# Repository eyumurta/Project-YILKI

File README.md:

This is the first Prototype of Open Plc Controller Board Yılkı.This project devoloped with Eagle
Project started 2024.
First Protype doesn't have built in Power,mcu circuits. This PT1 is only creating for testing input,output and Rs485 line.
I'm not a hardware engineer so project maybe have faulty designs.This Board using Stm32f0 Discovery board to handle inputs and outputs.
You can see inputs state by LED.But power calculations are wrong so I'm not soldered the Leds and their resistors.In theory boards outputs can drive relay but not tested. 

Input Side:
Inputs Are Designed sink (0v Common).Protected by TVS diode and optocoupler.Added RC filter for ripples.

Output Side:
Outputs are Designed source(24V Common).Outputs Protected by Optocoupler and reverse diode for relay.

Full Duplex RS-485:
This circuit is Full Duplex Rs-485 line

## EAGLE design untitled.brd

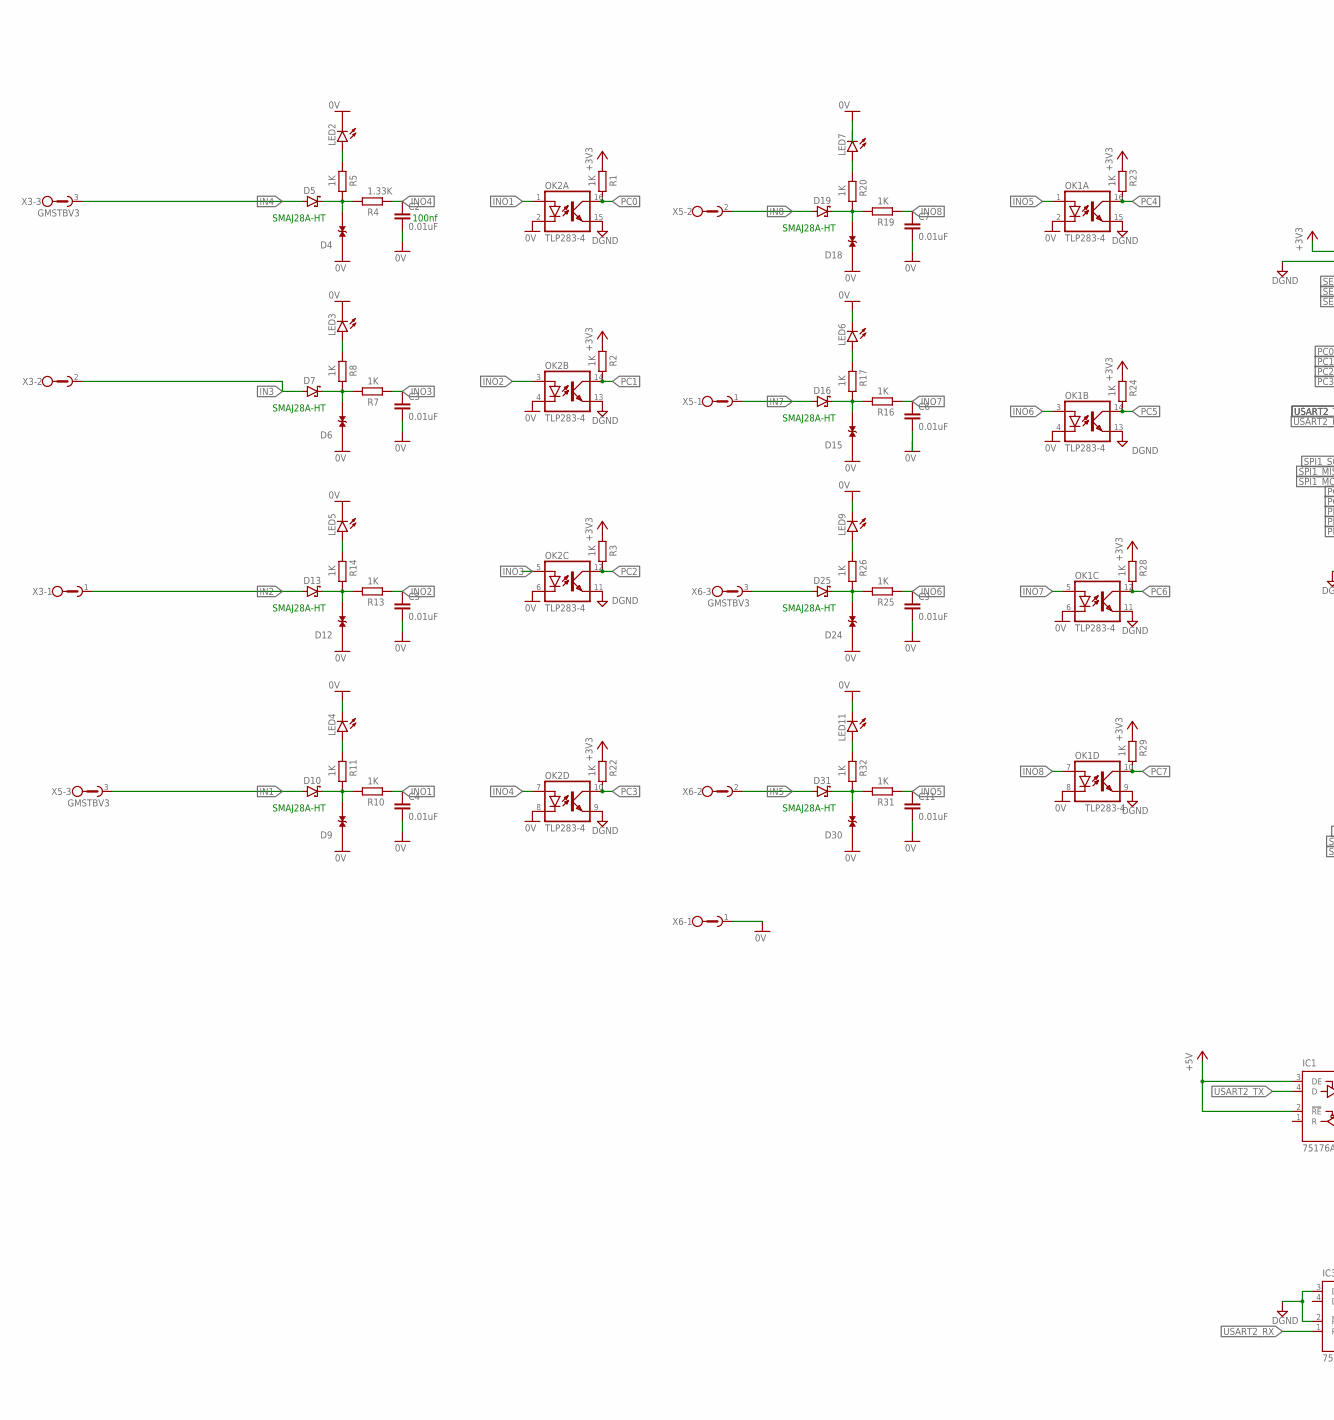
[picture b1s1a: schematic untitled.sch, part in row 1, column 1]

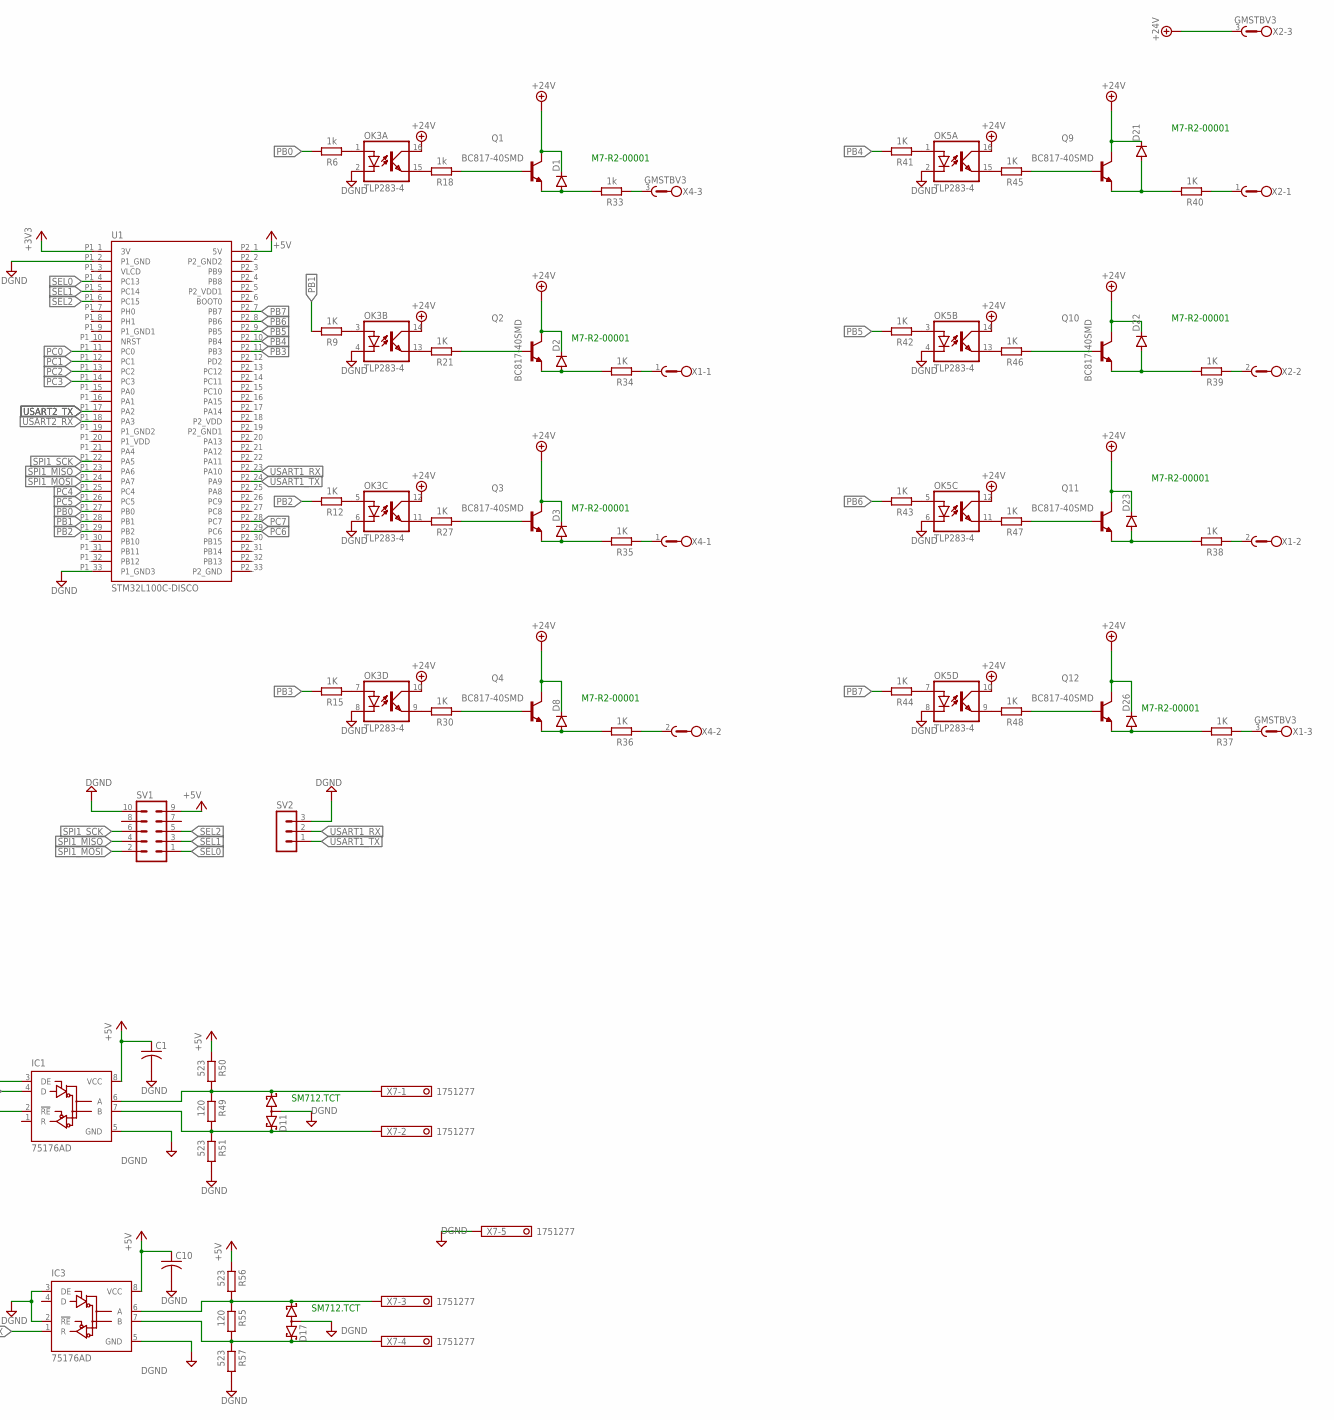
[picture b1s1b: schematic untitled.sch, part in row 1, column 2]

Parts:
C1, C10: C-USC0805; C0805
C2, C3, C4, C5, C6, C7, C9, C11: 0.01uF; C0805
D1, D2, D3, D8, D21, D22, D23, D26: S1M; SMA
D4, D6, D9, D12, D15, D18, D24, D30: SMAJ28CA; DIOM4325X250N
D5, D7, D10, D13, D16, D19, D25, D31: SCHOTTKY-DIODESMD; SMB
D11, D17: BAS40-06; SOT23
IC1, IC3: 75176AD; D_R-PDSO-G8
LED2, LED3, LED4, LED5, LED6, LED7, LED9, LED11: LEDCHIP-LED0805; CHIP-LED0805
OK1, OK2, OK3, OK5: TLP283-4; MINI-FLAT-16
Q1, Q2, Q3, Q4, Q9, Q10, Q11, Q12: BC817-40SMD; SOT23-BEC
R1, R2, R3, R5, R7, R8, R9, R10, R11, R12, R13, R14, R15, R16, R17, R19, R20, R21, R22, R23, R24, R25, R26, R27, R28, R29, R30, R31, R32, R34, R35, R36, R37, R38, R39, R40, R41, R42, R43, R44, R45, R46, R47, R48: 1K; R0805
R4: 1.33K; R0805
R6, R18, R33: 1k; R0805
R49, R55: 120; R0805
R50, R51, R56, R57: 523; R0805
SV1: MA05-2
SV2: MA03-1
U1: STM32L100C-DISCO; DEV_STM32L100C-DISCO
X1, X2, X3, X4, X5, X6: GMSTBV3
X7: 1751277

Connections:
0V: C2.2, C3.2, C4.2, C5.2, C6.2, C7.2, C9.2, C11.2, D4.1, D6.1, D9.1, D12.1, D15.1, D18.1, D24.1, D30.1, LED2.C, LED3.C, LED4.C, LED5.C, LED6.C, LED7.C, LED9.C, LED11.C, OK1.2 (C), OK1.4 (C), OK1.6 (C), OK1.8 (C), OK2.2 (C), OK2.4 (C), OK2.6 (C), OK2.8 (C), X6.1
+3V3: R1.2, R2.2, R3.2, R22.2, R23.2, R24.2, R28.2, R29.2, U1.P1_1 (3V)
+5V: C1.1, C10.1, IC1.2 (!RE), IC1.3 (DE), IC1.8 (VCC), IC3.8 (VCC), R50.2, R56.2, SV1.9, U1.P2_1 (5V)
+24V: D1.C, D2.C, D3.C, D8.C, D21.C, D22.C, D23.C, D26.C, OK3.10 (COL), OK3.12 (COL), OK3.14 (COL), OK3.16 (COL), OK5.10 (COL), OK5.12 (COL), OK5.14 (COL), OK5.16 (COL), Q1.C, Q2.C, Q3.C, Q4.C, Q9.C, Q10.C, Q11.C, Q12.C, X2.3
DGND: C1.2, C10.2, D11.3 (AA), D17.3 (AA), IC1.5 (GND), IC3.2 (!RE), IC3.3 (DE), IC3.5 (GND), OK1.9 (EMIT), OK1.11 (EMIT), OK1.13 (EMIT), OK1.15 (EMIT), OK2.9 (EMIT), OK2.11 (EMIT), OK2.13 (EMIT), OK2.15 (EMIT), OK3.2 (C), OK3.4 (C), OK3.6 (C), OK3.8 (C), OK5.2 (C), OK5.4 (C), OK5.6 (C), OK5.8 (C), R51.1, R57.1, SV1.10, SV2.3, U1.P1_2 (P1_GND), U1.P1_33 (P1_GND3), X7.5
IN1: D10.A, X5.3
IN2: D13.A, X3.1
IN3: D7.A, X3.2
IN4: D5.A, X3.3
IN5: D31.A, X6.2
IN7: D16.A, X5.1
IN8: D19.A, X5.2
INO1: C4.1, OK2.1 (A), R10.2
INO2: C5.1, OK2.3 (A), R13.2
INO3: C3.1, OK2.5 (A), R7.2
INO4: C2.1, OK2.7 (A), R4.2
INO5: C11.1, OK1.1 (A), R31.2
INO6: C9.1, OK1.3 (A), R25.2
INO7: C6.1, OK1.5 (A), R16.2
INO8: C7.1, OK1.7 (A), R19.2
unnamed: LED2.A, R5.2
unnamed: LED3.A, R8.2
unnamed: LED4.A, R11.2
unnamed: LED5.A, R14.2
unnamed: LED6.A, R17.2
unnamed: LED7.A, R20.2
unnamed: LED9.A, R26.2
unnamed: LED11.A, R32.2
unnamed: D4.2, D5.C, R4.1, R5.1
unnamed: D6.2, D7.C, R7.1, R8.1
unnamed: D12.2, D13.C, R13.1, R14.1
unnamed: D9.2, D10.C, R10.1, R11.1
unnamed: D18.2, D19.C, R19.1, R20.1
unnamed: D15.2, D16.C, R16.1, R17.1
unnamed: D24.2, D25.C, R25.1, R26.1
unnamed: D30.2, D31.C, R31.1, R32.1
unnamed: OK3.1 (A), R6.2
unnamed: OK3.3 (A), R9.2
unnamed: OK3.5 (A), R12.2
unnamed: OK3.7 (A), R15.2
unnamed: OK3.15 (EMIT), R18.1
unnamed: OK3.13 (EMIT), R21.1
unnamed: OK3.11 (EMIT), R27.1
unnamed: OK3.9 (EMIT), R30.1
unnamed: Q4.B, R30.2
unnamed: Q3.B, R27.2
unnamed: Q2.B, R21.2
unnamed: Q1.B, R18.2
unnamed: R33.2, X4.3
unnamed: R34.2, X1.1
unnamed: R35.2, X4.1
unnamed: D25.A, X6.3
unnamed: OK5.1 (A), R41.2
unnamed: OK5.15 (EMIT), R45.1
unnamed: OK5.3 (A), R42.2
unnamed: OK5.13 (EMIT), R46.1
unnamed: OK5.5 (A), R43.2
unnamed: OK5.11 (EMIT), R47.1
unnamed: OK5.7 (A), R44.2
unnamed: OK5.9 (EMIT), R48.1
unnamed: D1.A, Q1.E, R33.1
unnamed: R36.2, X4.2
unnamed: D2.A, Q2.E, R34.1
unnamed: D3.A, Q3.E, R35.1
unnamed: D8.A, Q4.E, R36.1
unnamed: D26.A, Q12.E, R37.1
unnamed: D23.A, Q11.E, R38.1
unnamed: D22.A, Q10.E, R39.1
unnamed: Q12.B, R48.2
unnamed: Q11.B, R47.2
unnamed: Q10.B, R46.2
unnamed: Q9.B, R45.2
unnamed: R37.2, X1.3
unnamed: R38.2, X1.2
unnamed: R39.2, X2.2
unnamed: R40.2, X2.1
unnamed: D21.A, Q9.E, R40.1
unnamed: D11.1 (K1), IC1.6 (A), R49.2, R50.1, X7.1
unnamed: D11.2 (K2), IC1.7 (B), R49.1, R51.2, X7.2
unnamed: D17.1 (K1), IC3.6 (A), R55.2, R56.1, X7.3
unnamed: D17.2 (K2), IC3.7 (B), R55.1, R57.2, X7.4
P1_GND1: U1.P1_9 (P1_GND1)
P1_GND2: U1.P1_19 (P1_GND2)
P1_VDD: U1.P1_20 (P1_VDD)
P2_GND: U1.P2_33 (P2_GND)
P2_GND1: U1.P2_19 (P2_GND1)
P2_GND2: U1.P2_2 (P2_GND2)
P2_VDD: U1.P2_18 (P2_VDD)
P2_VDD1: U1.P2_5 (P2_VDD1)
PB0: R6.1, U1.P1_27 (PB0)
PB1: R9.1, U1.P1_28 (PB1)
PB2: R12.1, U1.P1_29 (PB2)
PB3: R15.1, U1.P2_11 (PB3)
PB4: R41.1, U1.P2_10 (PB4)
PB5: R42.1, U1.P2_9 (PB5)
PB6: R43.1, U1.P2_8 (PB6)
PB7: R44.1, U1.P2_7 (PB7)
PC0: OK2.16 (COL), R1.1, U1.P1_11 (PC0)
PC1: OK2.14 (COL), R2.1, U1.P1_12 (PC1)
PC2: OK2.12 (COL), R3.1, U1.P1_13 (PC2)
PC3: OK2.10 (COL), R22.1, U1.P1_14 (PC3)
PC4: OK1.16 (COL), R23.1, U1.P1_25 (PC4)
PC5: OK1.14 (COL), R24.1, U1.P1_26 (PC5)
PC6: OK1.12 (COL), R28.1, U1.P2_29 (PC6)
PC7: OK1.10 (COL), R29.1, U1.P2_28 (PC7)
SEL0: SV1.1, U1.P1_4 (PC13)
SEL1: SV1.3, U1.P1_5 (PC14)
SEL2: SV1.5, U1.P1_6 (PC15)
SPI1_MISO: SV1.4, U1.P1_23 (PA6)
SPI1_MOSI: SV1.2, U1.P1_24 (PA7)
SPI1_SCK: SV1.6, U1.P1_22 (PA5)
USART1_RX: SV2.2, U1.P2_23 (PA10)
USART1_TX: SV2.1, U1.P2_24 (PA9)
USART2_RX: IC3.1 (R), U1.P1_18 (PA3)
USART2_TX: IC1.4 (D), U1.P1_17 (PA2)
VLCD: U1.P1_3 (VLCD)

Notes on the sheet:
SMAJ28A-HT
M7-R2-00001
SM712.TCT
100nf

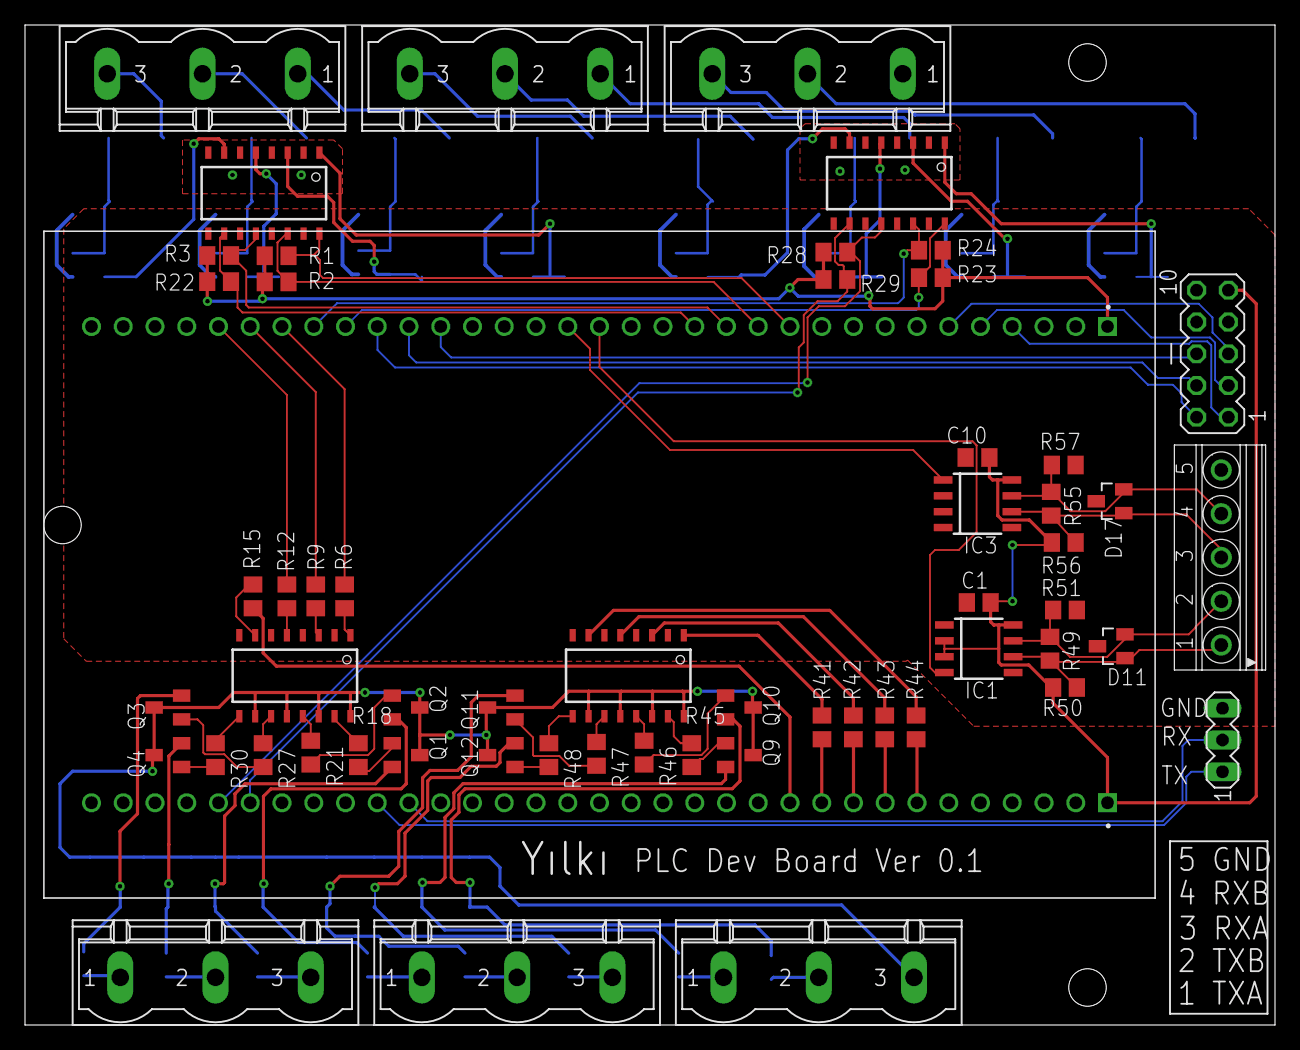
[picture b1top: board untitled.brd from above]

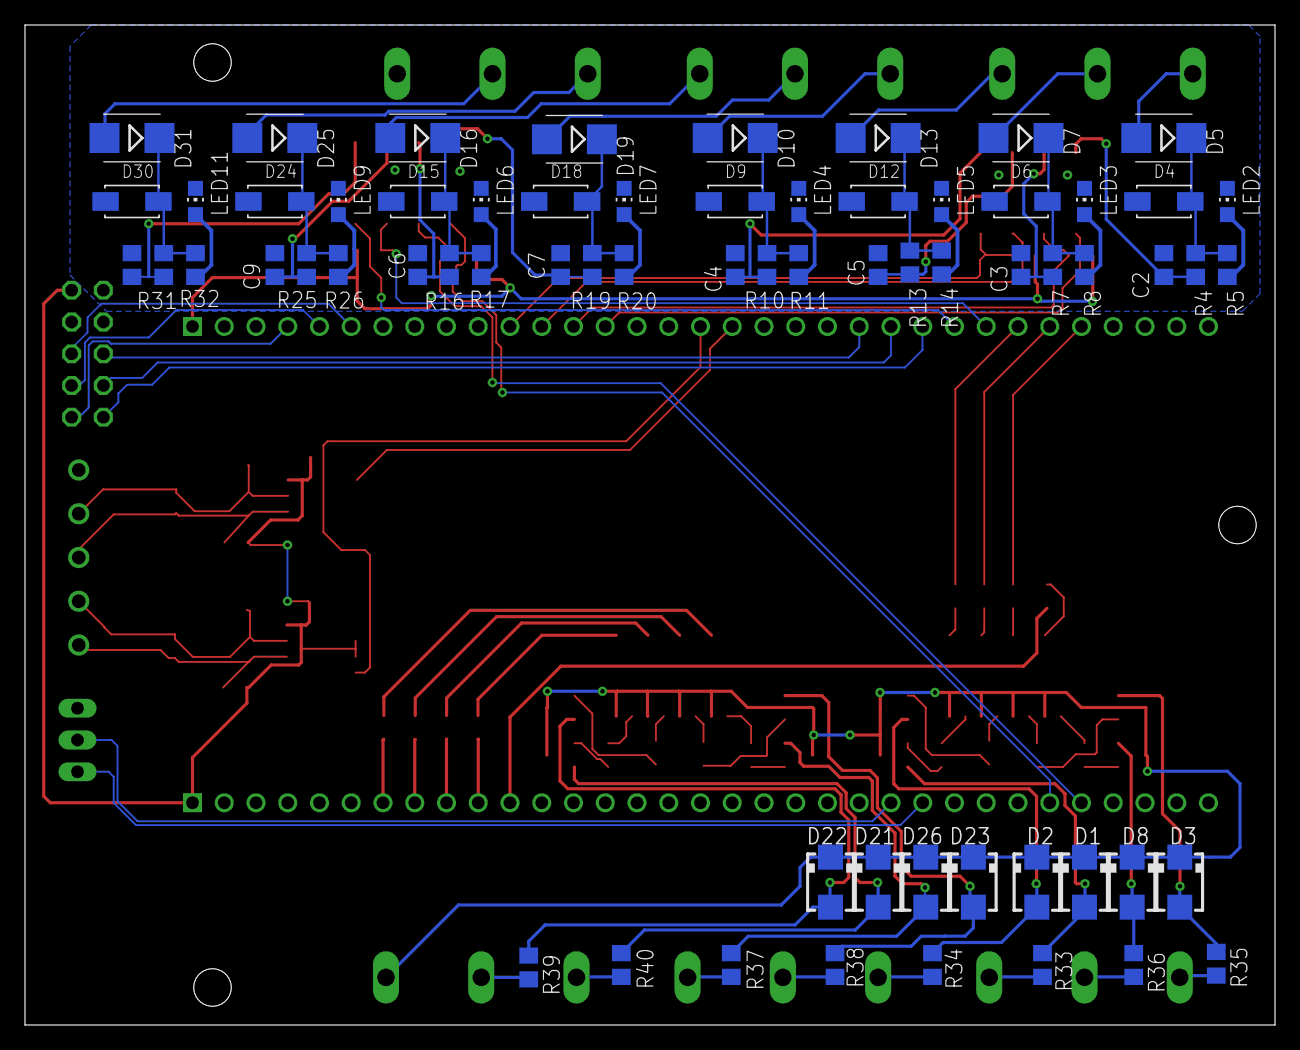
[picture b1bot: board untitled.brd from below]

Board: 2 copper layers, 100.0 x 80.0 mm, 122 parts (64 on the bottom side), 107 nets.

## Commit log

2025-02-15 First upload Yılkı PT1
2025-02-15 Create Pictures
2025-02-15 Pictures
